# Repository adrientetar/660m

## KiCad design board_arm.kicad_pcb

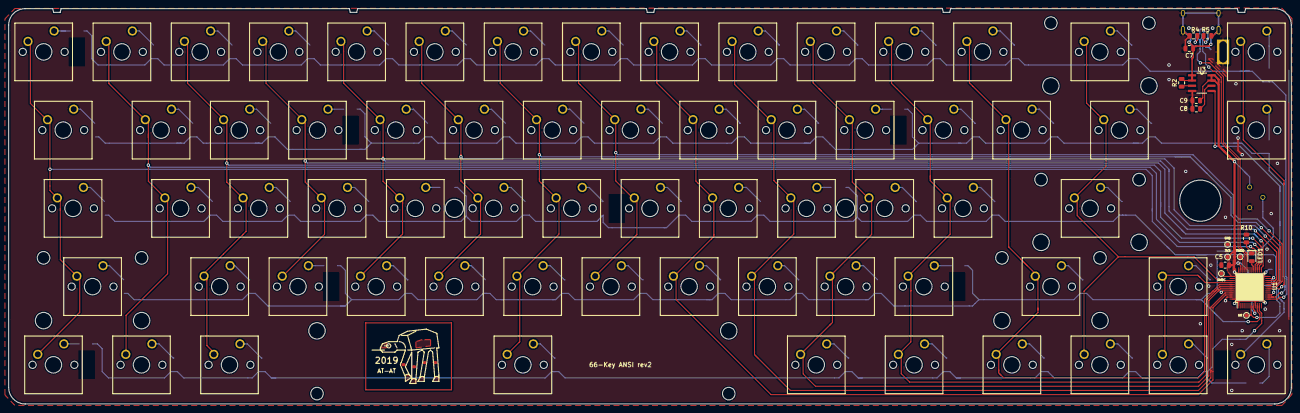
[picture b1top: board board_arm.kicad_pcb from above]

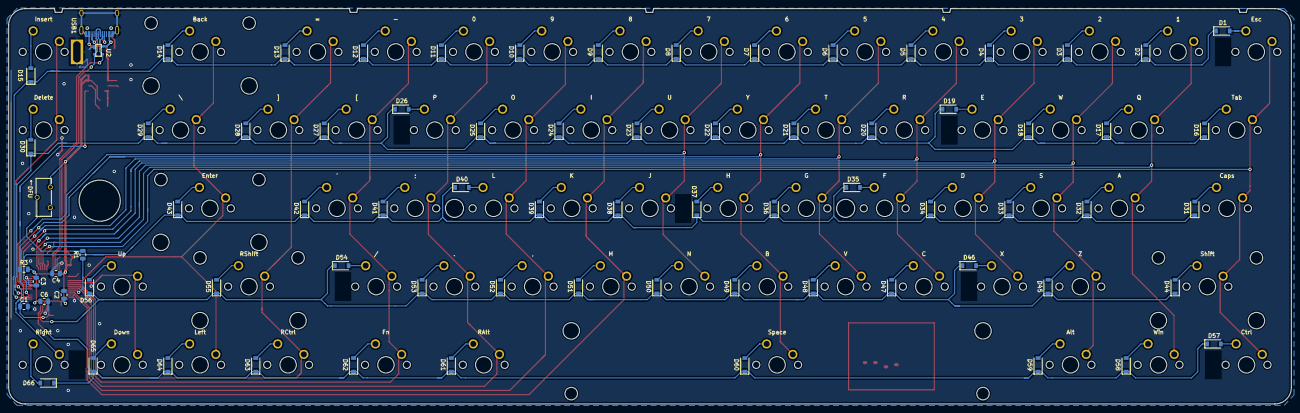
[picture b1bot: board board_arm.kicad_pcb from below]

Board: 2 copper layers, 311.5 x 96.0 mm, 167 parts (76 on the bottom side), 103 nets.

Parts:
3V3: TestPoint; TestPoint_Pad_D1.0mm
C1, C2, C3, C4: 0.1uF; C_0805_2012Metric
C5: 4.7uF; C_0805_2012Metric
C6: 10nF; C_0805_2012Metric
C7, C9: 10uF; C_0805_2012Metric
C8: 1nF; C_0805_2012Metric
D1, D2, D3, D4, D5, D6, D7, D8, D9, D10, D11, D12, D13, D14, D15, D16, D17, D18, D19, D20, D21, D22, D23, D24, D25, D26, D27, D28, D29, D30, D31, D32, D33, D34, D35, D36, D37, D38, D39, D40, D41, D42, D43, D44, D45, D46, D47, D48, D49, D50, D51, D52, D53, D54, D55, D56, D57, D58, D59, D60, D61, D62, D63, D64, D65, D66: SOD-123; D_SOD-123
GND: TestPoint; TestPoint_Pad_D1.0mm
H1, H2, H3, H4, H5, H6, H7, H8: Leopold-MountingHole
H9: Leopold-MountingPad
K_#0: 0; MX-1U-19mm
K_#1: 1; MX-1U-19mm
K_#2: 2; MX-1U-19mm
K_#3: 3; MX-1U-19mm
K_#4: 4; MX-1U-19mm
K_#5: 5; MX-1U-19mm
K_#6: 6; MX-1U-19mm
K_#7: 7; MX-1U-19mm
K_#8: 8; MX-1U-19mm
K_#9: 9; MX-1U-19mm
K_'1: '; MX-1U-19mm
K_,1: ,; MX-1U-19mm
K_-1: -; MX-1U-19mm
K_.1: .; MX-1U-19mm
K_/1: /; MX-1U-19mm
K_;1: ;; MX-1U-19mm
K_=1: =; MX-1U-19mm
K_A1: A; MX-1U-19mm
K_ALT1: Alt; MX-1.25U-19mm
K_B1: B; MX-1U-19mm
K_BACK1: Back; MX-2U-19mm
K_C1: C; MX-1U-19mm
K_CAPS1: Caps; MX-1.75U-19mm
K_CTRL1: Ctrl; MX-1.25U-19mm
K_D1: D; MX-1U-19mm
K_DELETE1: Delete; MX-1U-19mm
K_DOWN1: Down; MX-1U-19mm
K_E1: E; MX-1U-19mm
K_ENTER1: Enter; MX-2.25U-19mm
K_ESC1: Esc; MX-1U-19mm
K_F1: F; MX-1U-19mm
K_FN1: Fn; MX-1.25U-19mm
K_G1: G; MX-1U-19mm
K_H1: H; MX-1U-19mm
K_I1: I; MX-1U-19mm
K_INSERT1: Insert; MX-1U-19mm
K_J1: J; MX-1U-19mm
K_K1: K; MX-1U-19mm
K_L1: L; MX-1U-19mm
K_LEFT1: Left; MX-1U-19mm
K_M1: M; MX-1U-19mm
K_N1: N; MX-1U-19mm
K_O1: O; MX-1U-19mm
K_P1: P; MX-1U-19mm
K_Q1: Q; MX-1U-19mm
K_R1: R; MX-1U-19mm
K_RALT1: RAlt; MX-1.25U-19mm
K_RCTRL1: RCtrl; MX-1.25U-19mm
K_RIGHT1: Right; MX-1U-19mm
K_RSHIFT1: RShift; MX-2.25U-19mm
K_S1: S; MX-1U-19mm
K_SHIFT1: Shift; MX-2.25U-19mm
K_SPACE1: Space; MX-6.25U-19mm
K_T1: T; MX-1U-19mm
K_TAB1: Tab; MX-1.5U-19mm
K_U1: U; MX-1U-19mm
K_UP1: Up; MX-1U-19mm
K_V1: V; MX-1U-19mm
K_W1: W; MX-1U-19mm
K_WIN1: Win; MX-1U-19mm
K_X1: X; MX-1U-19mm
K_Y1: Y; MX-1U-19mm
K_Z1: Z; MX-1U-19mm
K_[1: [; MX-1U-19mm
K_\1: \; MX-1.5U-19mm
K_]1: ]; MX-1U-19mm
LED1: LED; LED_0805_2012Metric
NR: TestPoint; TestPoint_Pad_D1.0mm
R1, R2, R3: 10k; R_0805_2012Metric
R4, R5: 5.1k; R_0805_2012Metric
R10: 1k; R_0805_2012Metric
SW1: DFU; SW_SPDT_9.0x3.5mm
SWDC: TestPoint; TestPoint_Pad_D1.0mm
SWDD: TestPoint; TestPoint_Pad_D1.0mm
U1: STM32F072CBT6; LQFP-48_7x7mm_P0.5mm
U2: PRTR5V0U2X; SOT143B
U3: MCP1725-3302E_SN
USB1: HRO-TYPE-C-31-M-12; HRO-TYPE-C-31-M-12-Assembly

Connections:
+3V3: 3V3.1, C2.1, C3.1, C4.1, C5.1, C6.1, C9.1, R3.2, SW1.3, U1.1, U1.9, U1.24, U1.36, U1.48, U3.7, U3.8
+5V: C7.1, R2.1, U2.4, U3.1, U3.2, USB1.2, USB1.11
COL0: K_CAPS1.1, K_CTRL1.1, K_ESC1.1, K_SHIFT1.1, K_TAB1.1, U1.28
COL1: K_#1.1, K_A1.1, K_Q1.1, K_WIN1.1, U1.27
COL2: K_#2.1, K_ALT1.1, K_S1.1, K_W1.1, K_Z1.1, U1.26
COL3: K_#3.1, K_D1.1, K_E1.1, K_X1.1, U1.25
COL4: K_#4.1, K_C1.1, K_F1.1, K_R1.1, U1.22
COL5: K_#5.1, K_G1.1, K_T1.1, K_V1.1, U1.21
COL6: K_#6.1, K_B1.1, K_H1.1, K_SPACE1.1, K_Y1.1, U1.20
COL7: K_#7.1, K_J1.1, K_N1.1, K_U1.1, U1.19
COL8: K_#8.1, K_I1.1, K_K1.1, K_M1.1, U1.46
COL9: K_#9.1, K_,1.1, K_L1.1, K_O1.1, U1.45
COL10: K_#0.1, K_.1.1, K_;1.1, K_P1.1, K_RALT1.1, U1.43
COL11: K_'1.1, K_-1.1, K_/1.1, K_FN1.1, K_[1.1, U1.42
COL12: K_=1.1, K_RCTRL1.1, K_RSHIFT1.1, K_]1.1, U1.41
COL13: K_BACK1.1, K_ENTER1.1, K_LEFT1.1, K_\1.1, U1.39
COL14: K_DOWN1.1, K_UP1.1, U1.40
COL15: K_DELETE1.1, K_INSERT1.1, K_RIGHT1.1, U1.18
D+: U1.33, U2.2, USB1.6, USB1.8
D-: U1.32, U2.3, USB1.5, USB1.7
GND: C1.2, C2.2, C3.2, C4.2, C5.2, C6.2, C7.2, C8.2, C9.2, GND.1, R4.1, R5.1, R10.1, SW1.1, U1.8, U1.23, U1.35, U1.47, U2.1, U3.4, USB1.1, USB1.12, USB1.13
unnamed: C8.1, U3.6
unnamed: D1.2, K_ESC1.2
unnamed: D2.2, K_#1.2
unnamed: D3.2, K_#2.2
unnamed: D4.2, K_#3.2
unnamed: D5.2, K_#4.2
unnamed: D6.2, K_#5.2
unnamed: D7.2, K_#6.2
unnamed: D8.2, K_#7.2
unnamed: D9.2, K_#8.2
unnamed: D10.2, K_#9.2
unnamed: D11.2, K_#0.2
unnamed: D12.2, K_-1.2
unnamed: D13.2, K_=1.2
unnamed: D14.2, K_BACK1.2
unnamed: D15.2, K_INSERT1.2
unnamed: D16.2, K_TAB1.2
unnamed: D17.2, K_Q1.2
unnamed: D18.2, K_W1.2
unnamed: D19.2, K_E1.2
unnamed: D20.2, K_R1.2
unnamed: D21.2, K_T1.2
unnamed: D22.2, K_Y1.2
unnamed: D23.2, K_U1.2
unnamed: D24.2, K_I1.2
unnamed: D25.2, K_O1.2
unnamed: D26.2, K_P1.2
unnamed: D27.2, K_[1.2
unnamed: D28.2, K_]1.2
unnamed: D29.2, K_\1.2
unnamed: D30.2, K_DELETE1.2
unnamed: D31.2, K_CAPS1.2
unnamed: D32.2, K_A1.2
unnamed: D33.2, K_S1.2
unnamed: D34.2, K_D1.2
unnamed: D35.2, K_F1.2
unnamed: D36.2, K_G1.2
unnamed: D37.2, K_H1.2
unnamed: D38.2, K_J1.2
unnamed: D39.2, K_K1.2
unnamed: D40.2, K_L1.2
unnamed: D41.2, K_;1.2
unnamed: D42.2, K_'1.2
unnamed: D43.2, K_ENTER1.2
unnamed: D44.2, K_SHIFT1.2
unnamed: D45.2, K_Z1.2
unnamed: D46.2, K_X1.2
unnamed: D47.2, K_C1.2
unnamed: D48.2, K_V1.2
unnamed: D49.2, K_B1.2
unnamed: D50.2, K_N1.2
unnamed: D51.2, K_M1.2
unnamed: D52.2, K_,1.2
unnamed: D53.2, K_.1.2
unnamed: D54.2, K_/1.2
unnamed: D55.2, K_RSHIFT1.2
unnamed: D56.2, K_UP1.2
unnamed: D57.2, K_CTRL1.2
unnamed: D58.2, K_WIN1.2
unnamed: D59.2, K_ALT1.2
unnamed: D60.2, K_SPACE1.2
unnamed: D61.2, K_RALT1.2
unnamed: D62.2, K_FN1.2
unnamed: D63.2, K_RCTRL1.2
unnamed: D64.2, K_LEFT1.2
unnamed: D65.2, K_DOWN1.2
unnamed: D66.2, K_RIGHT1.2
unnamed: LED1.1, R10.2
unnamed: LED1.2, U1.29
unnamed: R1.1, U1.44
unnamed: R1.2, SW1.2
unnamed: R2.2, U3.3
unnamed: R4.2, USB1.4
unnamed: R5.2, USB1.10
PWRGD: C1.1, NR.1, R3.1, U1.7, U3.5
ROW0: D1.1, D2.1, D3.1, D4.1, D5.1, D6.1, D7.1, D8.1, D9.1, D10.1, D11.1, D12.1, D13.1, D14.1, D15.1, U1.13
ROW1: D16.1, D17.1, D18.1, D19.1, D20.1, D21.1, D22.1, D23.1, D24.1, D25.1, D26.1, D27.1, D28.1, D29.1, D30.1, U1.14
ROW2: D31.1, D32.1, D33.1, D34.1, D35.1, D36.1, D37.1, D38.1, D39.1, D40.1, D41.1, D42.1, D43.1, U1.15
ROW3: D44.1, D45.1, D46.1, D47.1, D48.1, D49.1, D50.1, D51.1, D52.1, D53.1, D54.1, D55.1, D56.1, U1.10
ROW4: D57.1, D58.1, D59.1, D60.1, D61.1, D62.1, D63.1, D64.1, D65.1, D66.1, U1.11
SWDCLK: SWDC.1, U1.37
SWDIO: SWDD.1, U1.34

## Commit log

2019-02-11 Schematic
2019-02-12 Generated PCB
2019-02-13 PCB layout first pass
2019-02-14 Fixes
2019-02-14 More fixes
2019-02-16 Fix ESD diode, ready to route
2019-02-16 Switches horizontal wiring
2019-02-16 Vertical routing
2019-02-16 Route around USB, missing fuse
2019-02-19 ARM schematics
2019-02-19 ARM board
2019-02-19 Fix MCU wires
2019-02-19 Pretty
2019-02-19 Add switch footprint
2019-02-20 rerouting of the USB and reg
2019-02-20 basic routing of sigs and power supply
2019-02-20 corrections sur les TP
2019-02-20 correction sur un condo. alim terminée. reste à tirer les signaux ligne et col
2019-02-21 pcb art > lunch
2019-02-21 Regen netlist and add missing switch and routes
2019-02-21 Update fill shapes
2019-02-21 Cleanup tiny tracks
2019-02-21 More cleanup
2019-02-22 Add reset cap
2019-02-23 Renumber the caps
2019-02-25 décalage du MCU pour raisons religieuses et décalage de la ligne powergood pour raisons de compliance avec l'USB
2019-02-25 routage premiere version
2019-02-25 petites corrections
2019-03-02 kleine Verbesserungen
2019-03-08 deplacement switch, ajout LED, correction DRC
2019-03-09 Cleanups
2019-03-09 More
2019-03-11 Ajout de TP GND, 3V3 et reset pour SWD
2019-03-14 Adjust board measurements and position, add extra holes, move some traces to fit, reverse space stab holes
2019-03-21 decalage à gauche du MCU de 20 mil et reroutage
2019-03-21 Fix pcb measurement
2019-03-22 Add mounting holes and reroute
2019-03-23 Tweak positions according to print
2019-03-25 • Route around the new holes ✔️ • Refill ✔️ • Curse at the giant rectangle no-copper zones ✔️ • Glace absent-mindedly at the DRC ✔️ • Generate Gerbers ✔️
2019-03-25 Remove via place outside the board
2019-03-25 Make the hole next to USB into a GND pad, and regen fill zones
2019-04-17 Remove generated files
2019-04-18 Move around to 19mm pitch (from 19.05), fine-tune some holes placement
2019-04-19 added ground strips along the USB for compliance, moved the switch and added labels, moved some diodes that were too close to the edge
2019-04-19 fix ground shapes, fix DRC
2019-04-21 fix board
2019-04-22 Last-ditch tweaks
